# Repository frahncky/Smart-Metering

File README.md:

# Smart-Metering

Analisador trifásico de energia e qualidade de energia com interface gráfica touchscreen.

## Objetivo

Desenvolver um instrumento completo para medição, visualização e registro de grandezas elétricas em sistemas monofásicos e trifásicos, incluindo:

- tensões e correntes RMS por fase;
- potência ativa, reativa e aparente;
- fator de potência;
- frequência;
- energia importada e exportada;
- demanda;
- diagrama fasorial;
- sequência de fases;
- desequilíbrio de tensão e corrente;
- formas de onda;
- THD;
- espectro harmônico;
- registro de afundamentos, elevações, interrupções e outros eventos de qualidade de energia;
- armazenamento histórico;
- comunicação Ethernet, Wi-Fi e RS-485/Modbus;
- interface local em touchscreen de 7".

## Arquitetura inicial

```text
Rede elétrica
   |
   +--> Proteção e condicionamento de tensão ----+
   |                                             |
   +--> TCs / condicionamento de corrente -------+--> ADE9430
                                                        |
                                                        | SPI
                                                        v
                                              MCU de metrologia
                                                        |
                                              Interface isolada
                                                        |
                                                        v
                                                   ESP32-P4
                                                        |
                                            Touchscreen 7" + LVGL

                     +--> microSD
                     +--> RTC
                     +--> Ethernet
                     +--> RS-485 / Modbus
                     +--> Wi-Fi / Bluetooth via coprocessador
```

## Componentes centrais

- **ADE9430** — front-end de medição polifásica e qualidade de energia.
- **MCU ARM** — aquisição do ADE9430, cálculo complementar, gerenciamento metrológico, calibração e eventos.
- **ESP32-P4** — interface gráfica, touchscreen e serviços de alto nível.
- **ESP32-C6** — opção para Wi-Fi/Bluetooth quando necessário.
- **Touchscreen 7"** — alvo inicial: 1024 × 600, interface capacitiva.

A seleção final do MCU ARM, TCs, display, isoladores, fontes e conectores será feita antes do fechamento do esquemático.

## Estrutura do repositório

```text
Smart-Metering/
├── hardware/
│   ├── README.md
│   └── Smart-Metering/
│       ├── Smart-Metering.kicad_pro
│       ├── Smart-Metering.kicad_sch      # folha raiz hierárquica
│       ├── 01_Power_Input.kicad_sch … 09_Power_Supplies.kicad_sch
│       ├── Smart-Metering.kicad_pcb      # layout roteado (todas as ligações feitas; DRC do KiCad pendente)
│       ├── Smart-Metering.kicad_dru      # regras de isolação (clearance/creepage)
│       ├── SmartMetering.kicad_sym       # símbolos próprios
│       ├── sym-lib-table
│       └── 3d/                           # modelos 3D simplificados do projeto (gen3d.py)
├── modelo 3D/                            # gabinete: Onshape (FeatureScripts) e Fusion (montagem, STEP)
├── docs/                                 # arquitetura, requisitos, decisões, layout, revisões
├── AGENTS.md                             # papéis e regras de trabalho dos agentes
└── README.md
```

## Estado

**Fase 2 — esquemático completo da placa de metrologia (rev. 0.1, a revisar no KiCad).**

Todas as 9 folhas estão desenhadas e os sinais entre folhas foram conferidos (223 componentes):

| Folha | Conteúdo |
|---|---|
| `01_Power_Input` | Alimentação pelas fases medidas (OU de diodos, qualquer fase presente) ou entrada auxiliar, por montagem; AC/DC isolado RECOM RAC20-05SK/277 (85–305 VAC, 5 V / 4 A) → `VIN_ACDC` |
| `02_Voltage_Sensing` | 3 fases: fusível + varistor, divisor 1/1001 (5 × 200 kΩ + 1 kΩ), anti-aliasing 7,2 kHz; R201 liga neutro ao GND metrológico |
| `03_Current_Sensing` | IA/IB/IC/IN configuráveis por montagem: TC 333 mV (padrão), Rogowski ou SCT-013 de 1 V; TVS, anti-aliasing 7,2 kHz, pino de identificação; headers internos para conectores M8 de painel |
| `04_ADE9430` | ADE9430 (U401), desacoplamento, cristal 24,576 MHz, reset |
| `05_Metrology_MCU` | STM32F413RHT6 (mesma família da referência da biblioteca ADSW-PQ-CLS), HSE 8 MHz, RTC com LSE + CR2032, EEPROM de calibração 24LC64, SWD, LEDs |
| `06_Isolation` | Barreira reforçada logo após o ADE9430: ISO7762 + ISO7761, MCP3204 (ID dos sensores), ADuM6000 + TPS7A20 → `+3V3_ADE` |
| `07_HMI_Interface` | Conector para a placa HMI (ESP32-P4): +5V com PTC, UART, IRQ e EN |
| `08_Communications` | RS-485/Modbus isolada (ADM2587E) e USB-C de serviço (USB FS + carga) |
| `09_Power_Supplies` | OU de entradas 5 V, carregador chaveado BQ25895 (entrada até 3 A, I2C), `+3V3` (TPS63001) e `+5V` (TPS61022) |

A HMI (ESP32-P4 + ESP32-C6, display 7", Ethernet, Wi-Fi/BT, microSD) fica em placa separada (REQ-010). No protótipo: Espressif ESP32-P4-Function-EV-Board.

Componentes de terceiros usam os símbolos oficiais da biblioteca KiCad 10; a biblioteca `SmartMetering` guarda só os símbolos próprios. Referências numeradas por folha (1xx na folha 01, 2xx na 02, …).

### Próximos passos

Revisão completa em [`docs/REVISAO_ESQUEMATICO.md`](docs/REVISAO_ESQUEMATICO.md); as pendências P1–P9 estão resolvidas.

- Rodar o ERC no KiCad e revisar.
- Confirmações de compra: variante CP-40 do ADE9430, certificação reforçada do ADuM6000, encapsulamento do RAC20-05SK/277.
- Firmware: configurar o BQ25895 por I2C (ICHG, VREG, VINDPM) e desabilitar o VBUS sensing do OTG no STM32.
- Layout da PCB (ver [`docs/LAYOUT.md`](docs/LAYOUT.md)): placa roteada (domínio quente, lado seguro e ilha RS-485) com creepage de 8 mm na barreira; todas as ligações feitas (rev. 0.6); falta preencher as zonas e rodar o DRC do KiCad (inclui creepage); os avisos de largura esperados estão listados no LAYOUT. Todos os componentes têm modelo 3D.

## Bateria interna

Bateria Li-Po plana 1S recarregável, com NTC, carregada pelo BQ25895 com o medidor ligado à rede (folha 09, J901). Autonomia a definir; a meta anterior de 13 horas foi retirada. Ver [bateria e alimentação](docs/INTERNAL_BATTERY.md).

## Método de trabalho

Papéis dos agentes e regras de colaboração: [AGENTS.md](AGENTS.md). Etapas, revisão e rastreabilidade: [docs/WORKFLOW.md](docs/WORKFLOW.md). Decisões de projeto: [docs/DECISIONS.md](docs/DECISIONS.md). Dimensionamentos: [entradas de tensão](docs/VOLTAGE_SENSING.md), [fonte metrológica e clock](docs/POWER_CLOCK.md).

## Referências principais

- Analog Devices ADE9430: https://www.analog.com/en/products/ade9430.html
- Espressif ESP32-P4: https://documentation.espressif.com/esp32-p4_datasheet_en.html

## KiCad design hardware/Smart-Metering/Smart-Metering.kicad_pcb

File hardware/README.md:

# Hardware

## Projeto KiCad

O projeto principal está em:

```text
hardware/Smart-Metering/
```

Arquivos principais:

- `Smart-Metering.kicad_pro`
- `Smart-Metering.kicad_sch`
- `Smart-Metering.kicad_pcb`

## Organização planejada do esquemático

O esquemático será hierárquico.

Folhas previstas:

1. `Power_Input`
2. `Voltage_Sensing`
3. `Current_Sensing`
4. `ADE9430`
5. `Metrology_MCU`
6. `Isolation`
7. `HMI_Interface`
8. `Communications`
9. `Power_Supplies`

A primeira implementação deverá começar por `Power_Supplies`, `Voltage_Sensing`, `Current_Sensing` e `ADE9430`.

## Regras

- manter símbolos e footprints personalizados dentro do repositório;
- não usar caminhos absolutos para bibliotecas próprias;
- registrar no Git os arquivos `.kicad_pro`, `.kicad_sch` e `.kicad_pcb`;
- não registrar backups e arquivos locais do KiCad;
- documentar alterações importantes de hardware antes de iniciar layout.

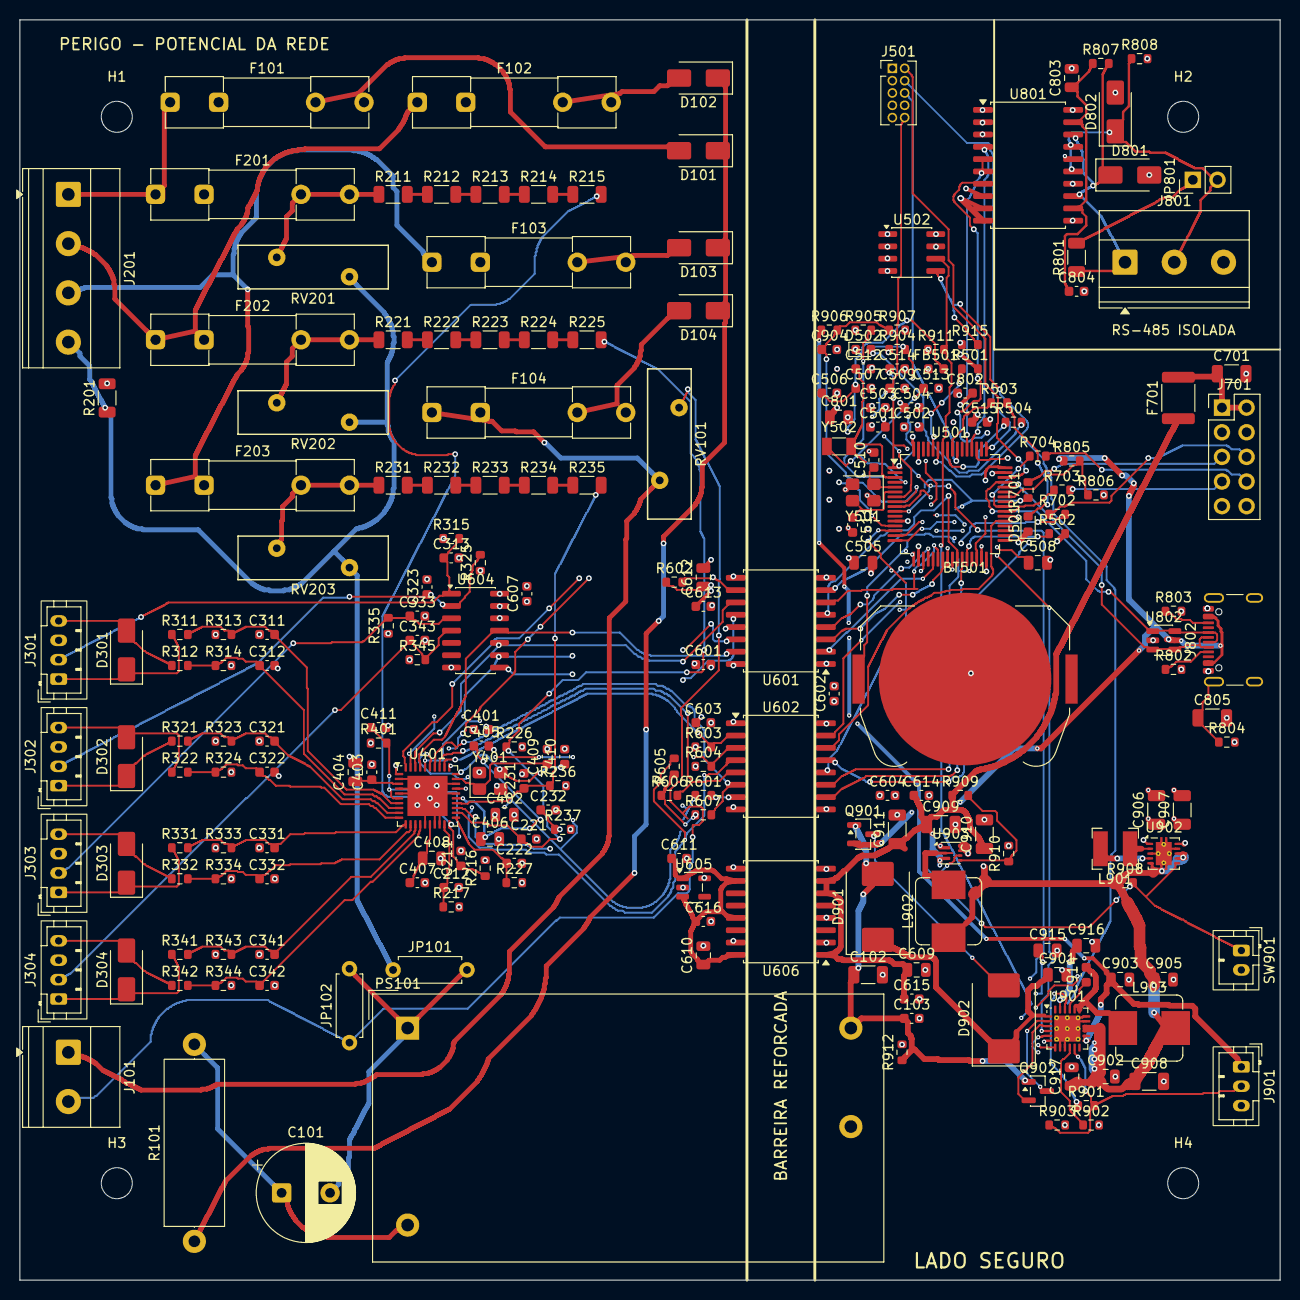
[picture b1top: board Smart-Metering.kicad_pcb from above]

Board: 4 copper layers, 130.0 x 130.0 mm, 230 parts (0 on the bottom side), 154 nets.

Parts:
BT501: CR2032; BatteryHolder_Keystone_3034_1x20mm
C101: 10uF 450V; CP_Radial_D10.0mm_P5.00mm
C102, C701, C906, C907, C908, C909, C910, C911: 22uF; C_1206_3216Metric
C103, C313, C323, C333, C343, C401, C403, C405, C407, C501, C502, C503, C504, C507, C509, C514, C515, C601, C602, C603, C604, C607, C613, C614, C615, C616, C802, C804, C904: 100nF; C_0603_1608Metric
C211, C212, C221, C222, C231, C232, C311, C312, C321, C322, C331, C332, C341, C342: 22nF C0G; C_0603_1608Metric
C402, C609, C610, C612, C801, C803, C901, C902, C903, C905, C916, C917: 10uF; C_0805_2012Metric
C404, C406, C408, C505, C508, C915: 4.7uF; C_0805_2012Metric
C409, C410, C512, C513: 10pF; C_0603_1608Metric
C411, C506, C611: 1uF; C_0603_1608Metric
C510, C511: 15pF; C_0603_1608Metric
C805: 4.7nF; C_1206_3216Metric
C914: 47nF; C_0603_1608Metric
D101, D102, D103, D104: S1M; D_SMA
D301, D302, D303, D304: SMAJ5.0CA; D_SMA
D501: green; LED_0603_1608Metric
D502: red; LED_0603_1608Metric
D801, D802: SMAJ12CA; D_SMA
D901, D902: SS54; D_SMC
F101, F102, F103, F104: T500mA 500VAC; Fuseholder_Clip-5x20mm_Littelfuse_111_Inline_P20.00x5.00mm_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
F201, F202, F203: 500mA 500VAC; Fuseholder_Clip-5x20mm_Littelfuse_111_Inline_P20.00x5.00mm_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
F701: PTC 2A; Fuse_1812_4532Metric
FB501: 600R@100MHz; L_0603_1608Metric
H1, H2, H3, H4: MountingHole_3.2mm_M3
J101: AUX L N; TerminalBlock_Phoenix_MKDS-1,5-2-5.08_1x02_P5.08mm_Horizont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
J201: VA VB VC VN; TerminalBlock_Phoenix_MKDS-1,5-4-5.08_1x04_P5.08mm_Horizont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
J301: SENSOR_IA; JST_PH_B4B-PH-K_1x04_P2.00mm_Vertical
J302: SENSOR_IB; JST_PH_B4B-PH-K_1x04_P2.00mm_Vertical
J303: SENSOR_IC; JST_PH_B4B-PH-K_1x04_P2.00mm_Vertical
J304: SENSOR_IN; JST_PH_B4B-PH-K_1x04_P2.00mm_Vertical
J501: SWD; PinHeader_2x05_P1.27mm_Vertical
J701: HMI_LINK; PinHeader_2x05_P2.54mm_Vertical
J801: RS485; TerminalBlock_Phoenix_MKDS-1,5-3-5.08_1x03_P5.08mm_Horizont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
J802: USB-C; USB_C_Receptacle_GCT_USB4105-xx-A_16P_TopMnt_Horizontal
J901: BATTERY_1S; JST_PH_B3B-PH-K_1x03_P2.00mm_Vertical
JP101, JP102: LINK; R_Axial_DIN0207_L6.3mm_D2.5mm_P7.62mm_Horizontal
JP801: TERM; PinHeader_1x02_P2.54mm_Vertical
L901: 2.2uH; L_Bourns-SRN4018
L902: 1uH; L_Bourns_SRP7028A_7.3x6.6mm
L903: 2.2uH; L_Bourns_SRP7028A_7.3x6.6mm
PS101: RAC20-05SK/277; Converter_ACDC_Recom_RAC20-xxSK_THT
Q901: AO3401A; SOT-23
Q902: 2N7002; SOT-23
R101: 22R 3W; R_Axial_DIN0617_L17.0mm_D6.0mm_P20.32mm_Horizontal
R201: 0R; R_1206_3216Metric
R211, R212, R213, R214, R215, R221, R222, R223, R224, R225, R231, R232, R233, R234, R235: 200k 0.1%; R_1206_3216Metric
R216, R217, R226, R227, R236, R237, R311, R312, R321, R322, R331, R332, R341, R342: 1k 0.1%; R_0603_1608Metric
R313, R314, R323, R324, R333, R334, R343, R344: 1M 0.1%; R_0603_1608Metric
R315, R325, R335, R345, R401, R501, R502, R602, R603, R604, R605, R606, R607, R805, R904, R905: 10k; R_0603_1608Metric
R503, R504, R601: 1k; R_0603_1608Metric
R701, R702, R703, R704: 33R; R_0603_1608Metric
R801: 120R; R_1206_3216Metric
R802, R803: 5.1k; R_0603_1608Metric
R804: 1M; R_0603_1608Metric
R806: 20k; R_0603_1608Metric
R807, R808: 680R; R_0603_1608Metric
R901: 5.23k; R_0603_1608Metric
R902: 120R; R_0603_1608Metric
R903: 30.1k; R_0603_1608Metric
R906, R907, R908, R910, R912: 100k; R_0603_1608Metric
R909: 732k; R_0603_1608Metric
R911, R915: 4.7k; R_0603_1608Metric
RV101, RV201, RV202, RV203: 320VAC 14mm; RV_Disc_D15.5mm_W4.5mm_P7.5mm
SW901: POWER; JST_PH_B2B-PH-K_1x02_P2.00mm_Vertical
U401: ADE9430ACPZ; Texas_RHA0040B_VQFN-40-1EP_6x6mm_P0.5mm_EP4.15x4.15mm
U501: STM32F413RHT6; LQFP-64_10x10mm_P0.5mm
U502: 24LC64; SOIC-8_3.9x4.9mm_P1.27mm
U601: ISO7762DW; SOIC-16W_7.5x10.3mm_P1.27mm
U602: ISO7761DW; SOIC-16W_7.5x10.3mm_P1.27mm
U604: MCP3204; SOIC-14_3.9x8.7mm_P1.27mm
U605: TPS7A2033PDBVR; SOT-23-5
U606: ADuM6000; SOIC-16W_7.5x10.3mm_P1.27mm
U801: ADM2587E; SOIC-20W_7.5x12.8mm_P1.27mm
U802: USBLC6-2SC6; SOT-23-6
U901: BQ25895RTW; Texas_RTW_WQFN-24-1EP_4x4mm_P0.5mm_EP2.7x2.7mm_ThermalVias
U902: TPS63001; Texas_DRC0010J_ThermalVias
U903: TPS61022; Texas_RWU0007A_VQFN-7_2x2mm_P0.5mm
Y401: 24.576MHz; Crystal_SMD_3225-4Pin_3.2x2.5mm
Y501: 8MHz; Crystal_SMD_3225-4Pin_3.2x2.5mm
Y502: 32.768kHz; Crystal_SMD_3215-2Pin_3.2x1.5mm

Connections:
+3V3: C501.1, C502.1, C503.1, C504.1, C505.1, C515.1, C602.1, C604.1, C801.1, C802.1, C906.1, C907.1, FB501.1, J501.1, R904.1, R905.1, R911.1, R915.1, U501.19, U501.32, U501.48, U501.64, U502.8, U601.1, U602.16, U801.2, U801.8, U902.1, U902.10
+3V3_ADE: C401.1, C402.1, C601.1, C603.1, C607.1, C612.1, C613.1, R315.1, R325.1, R335.1, R345.1, R401.1, R602.1, R603.1, R604.1, R605.1, R606.1, R607.1, U401.1, U401.27, U601.16, U602.1, U604.13, U604.14, U605.5
+5V: C609.1, C614.1, C615.1, C909.1, C910.1, C911.1, F701.1, R909.1, U606.1, U606.6, U606.7, U903.3
/ADE9430/AVDDOUT: C405.1, C406.1, U401.25
/ADE9430/DVDDOUT: C403.1, C404.1, U401.3
/ADE9430/REF_ADE: C407.1, C408.1, U401.16
/ADE9430/XIN_ADE: C409.1, U401.29, Y401.1
/ADE9430/XOUT_ADE: C410.1, U401.30, Y401.3
/Communications/BUS_A: D801.1, J801.1, R801.1, R807.2, U801.13, U801.18
/Communications/BUS_B: D802.1, J801.2, JP801.2, R808.1, U801.15, U801.17
/Communications/CC1: J802.A5, R802.1
/Communications/CC2: J802.B5, R803.1
/Communications/GND_485: C803.2, C804.2, D801.2, D802.2, J801.3, R808.2, U801.11, U801.14, U801.16, U801.20
/Communications/TERM: JP801.1, R801.2
/Communications/USB_SHIELD: C805.1, J802.SH, R804.1
/Communications/VISO_485: C803.1, C804.1, R807.1, U801.12, U801.19
/HMI Interface/+5V_HMI: C701.1, F701.2, J701.1, J701.2
/HMI Interface/LINK_EN: J701.8, R704.2
/HMI Interface/LINK_IRQ: J701.7, R703.2
/HMI Interface/LINK_RX: J701.6, R702.1
/HMI Interface/LINK_TX: J701.5, R701.2
/Isolation/+5V_ISO: C610.1, C611.1, C616.1, U605.1, U605.3, U606.10, U606.13, U606.16
/Isolation/RESET_DRV: R601.2, U602.7
/Isolation/SS_SID: U601.12, U604.8
/Metrology MCU/BOOT0: R501.1, U501.60
/Metrology MCU/BOOT1: R502.1, U501.28
/Metrology MCU/HSE_IN: C510.1, U501.5, Y501.1
/Metrology MCU/HSE_OUT: C511.1, U501.6, Y501.3
/Metrology MCU/LED_PULSE: R504.1, U501.57
/Metrology MCU/LED_STAT: R503.1, U501.56
/Metrology MCU/LSE_IN: C512.1, U501.3, Y502.1
/Metrology MCU/LSE_OUT: C513.1, U501.4, Y502.2
/Metrology MCU/NRST: C509.1, J501.10, U501.7
/Metrology MCU/SWCLK: J501.4, U501.49
/Metrology MCU/SWDIO: J501.2, U501.46
/Metrology MCU/SWO: J501.6, U501.55
/Metrology MCU/VBAT_RTC: BT501.1, C514.1, U501.1
/Metrology MCU/VCAP: C508.1, U501.30
/Metrology MCU/VDDA: C506.1, C507.1, FB501.2, U501.13
/Power Input/HV_DC: C101.1, PS101.2, R101.2
/Power Input/HV_RTN: C101.2, JP101.2, JP102.2, PS101.1
/Power Input/L_AUX: F104.1, J101.1, RV101.1
/Power Input/N_AUX: J101.2, JP102.1, RV101.2
/Power Supplies/BAT_NTC: J901.2, R901.2, R903.1, U901.11
/Power Supplies/BB_L1: L901.1, U902.4
/Power Supplies/BB_L2: L901.2, U902.2
/Power Supplies/CHG_BTST: C914.1, U901.21
/Power Supplies/CHG_DM: Q902.2, U901.3
/Power Supplies/CHG_DP: Q902.3, U901.2
/Power Supplies/CHG_SW: C914.2, L903.1, U901.19, U901.20
/Power Supplies/FB_5V: R909.2, R910.1, U903.4
/Power Supplies/ILIM: R902.1, U901.10
/Power Supplies/PMID: C916.1, U901.23
/Power Supplies/PWR_EN: R908.2, SW901.1, U902.6, U903.5
/Power Supplies/REGN: C915.1, R901.1, U901.22
/Power Supplies/SW_5V: L902.2, U903.2
/Power Supplies/VBAT: C903.1, J901.1, R906.1, U901.13, U901.14
/Power Supplies/VBUS_SW: D902.2, Q901.3
/Power Supplies/VIN_CHG: C901.1, D901.1, D902.1, U901.1
/Power Supplies/VSYS: C902.1, C905.1, C908.1, C917.1, L902.1, L903.2, R908.1, U901.15, U901.16, U902.5, U902.7, U902.8, U903.6, U903.7
CF1_ADE: R606.2, U401.33, U602.5
CF2_ADE: R607.2, U401.34, U602.6
CHG_INT_N: R904.2, U501.10, U901.7
CHG_N: R905.2, U501.9, U901.4
DREADY_ADE: R604.2, U401.36, U602.3
GND: C211.2, C212.2, C221.2, C222.2, C231.2, C232.2, C311.1, C312.2, C313.2, C321.1, C322.2, C323.2, C331.1, C332.2, C333.2, C341.1, C342.2, C343.2, C401.2, C402.2, C403.2, C404.2, C405.2, C406.2, C407.2, C408.2, C409.2, C410.2, C411.2, C601.2, C603.2, C607.2, C610.2, C611.2, C612.2, C613.2, C616.2, J301.3, J302.3, J303.3, J304.3, R201.2, R216.2, R217.2, R226.2, R227.2, R236.2, R237.2, R313.1, R314.2, R323.1, R324.2, R333.1, R334.2, R343.1, R344.2, U401.2, U401.4, U401.5, U401.15, U401.17, U401.18, U401.26, U401.28, U401.41, U601.9, U602.8, U604.7, U604.12, U605.2, U606.9, U606.15, Y401.2, Y401.4
GND_SYS: BT501.2, C102.2, C103.2, C501.2, C502.2, C503.2, C504.2, C505.2, C506.2, C507.2, C508.2, C509.2, C510.2, C511.2, C512.2, C513.2, C514.2, C515.2, C602.2, C604.2, C609.2, C614.2, C615.2, C701.2, C801.2, C802.2, C805.2, C901.2, C902.2, C903.2, C904.2, C905.2, C906.2, C907.2, C908.2, C909.2, C910.2, C911.2, C915.2, C916.2, C917.2, D501.1, D502.1, J501.3, J501.5, J501.9, J701.3, J701.4, J701.9, J701.10, J802.A1, J802.A12, J802.B1, J802.B12, J901.3, PS101.4, R501.2, R502.2, R802.2, R803.2, R804.2, R806.2, R902.2, R903.2, R907.2, R910.2, R912.2, SW901.2, U501.12, U501.18, U501.31, U501.47, U501.63, U502.1, U502.2, U502.3, U502.4, U502.7, U601.8, U602.9, U606.2, U606.4, U606.8, U801.1, U801.3, U801.9, U801.10, U802.2, U901.8, U901.9, U901.17, U901.18, U901.25, U902.3, U902.9, U902.11, U903.1, Y501.2, Y501.4
HMI_EN: R704.1, U501.40
HMI_IRQ: R703.1, U501.39
HMI_RX: R702.2, U501.17
HMI_TX: R701.1, U501.16
I2C_SCL: R911.2, U501.58, U502.6, U901.5
I2C_SDA: R915.2, U501.59, U502.5, U901.6
IAN: C312.1, R312.2, R314.1, U401.8
IAP: C311.2, R311.2, R313.2, U401.7
IBN: C322.1, R322.2, R324.1, U401.10
IBP: C321.2, R321.2, R323.2, U401.9
ICN: C332.1, R332.2, R334.1, U401.12
ICP: C331.2, R331.2, R333.2, U401.11
INN: C342.1, R342.2, R344.1, U401.14
INP: C341.2, R341.2, R343.2, U401.13
IRQ0_ADE: R602.2, U401.31, U601.10
IRQ1_ADE: R603.2, U401.32, U602.2
LINE_A: F101.1, F201.1, J201.1
LINE_B: F102.1, F202.1, J201.2
LINE_C: F103.1, F203.1, J201.3
MCU_CF1: U501.14, U602.12
MCU_CF2: U501.15, U602.11
MCU_DREADY: U501.37, U602.14
MCU_IRQ0: U501.24, U601.7
MCU_IRQ1: U501.25, U602.15
MCU_MISO: U501.22, U601.6
MCU_MOSI: U501.23, U601.3
MCU_RESET_ADE: U501.27, U602.10
MCU_SCLK: U501.21, U601.2
MCU_SS_ADE: U501.20, U601.4
MCU_SS_SID: U501.26, U601.5
MCU_ZX: U501.38, U602.13
MISO_ADE: U401.38, U601.11, U604.10
MOSI_ADE: U401.39, U601.14, U604.9
NEUTRAL: J201.4, JP101.1, R201.1, RV201.2, RV202.2, RV203.2
unnamed: D101.1, D102.1, D103.1, D104.1, R101.1
unnamed: D101.2, F101.2
unnamed: D102.2, F102.2
unnamed: D103.2, F103.2
unnamed: D104.2, F104.2
unnamed: D301.1, J301.1, R311.1
unnamed: D301.2, J301.4, R312.1
unnamed: D302.1, J302.1, R321.1
unnamed: D302.2, J302.4, R322.1
unnamed: D303.1, J303.1, R331.1
unnamed: D303.2, J303.4, R332.1
unnamed: D304.1, J304.1, R341.1
unnamed: D304.2, J304.4, R342.1
unnamed: D501.2, R503.2
unnamed: D502.2, R504.2
unnamed: F201.2, R211.1, RV201.1
unnamed: F202.2, R221.1, RV202.1
unnamed: F203.2, R231.1, RV203.1
unnamed: R211.2, R212.1
unnamed: R212.2, R213.1
unnamed: R213.2, R214.1
unnamed: R214.2, R215.1
unnamed: R221.2, R222.1
unnamed: R222.2, R223.1
unnamed: R223.2, R224.1
unnamed: R224.2, R225.1
unnamed: R231.2, R232.1
unnamed: R232.2, R233.1
unnamed: R233.2, R234.1
unnamed: R234.2, R235.1
RESET_ADE: C411.1, R401.2, R601.1, U401.6
RS485_DE: U501.53, U801.5, U801.6
RS485_RX: U501.52, U801.4
RS485_TX: U501.51, U801.7
SCLK_ADE: U401.37, U601.15, U604.11
SID_A: C313.1, J301.2, R315.2, U604.1
SID_B: C323.1, J302.2, R325.2, U604.2
SID_C: C333.1, J303.2, R335.2, U604.3
SID_N: C343.1, J304.2, R345.2, U604.4
SS_ADE: U401.40, U601.13
USB_DM: J802.A7, J802.B7, U501.44, U802.3, U802.4
USB_DP: J802.A6, J802.B6, U501.45, U802.1, U802.6
USB_VBUS_SENSE: R805.2, R806.1, U501.42
VAN: C212.1, R217.1, U401.19
VAP: C211.1, R215.2, R216.1, U401.20
VBAT_SENSE: C904.1, R906.2, R907.1, U501.8
VBN: C222.1, R227.1, U401.21
VBP: C221.1, R225.2, R226.1, U401.22
VBUS: J802.A4, J802.A9, J802.B4, J802.B9, Q901.2, R805.1, U802.5
VCN: C232.1, R237.1, U401.23
VCP: C231.1, R235.2, R236.1, U401.24
VIN_ACDC: C102.1, C103.1, D901.2, PS101.5, Q901.1, Q902.1, R912.1
ZX_ADE: R605.2, U401.35, U602.4
